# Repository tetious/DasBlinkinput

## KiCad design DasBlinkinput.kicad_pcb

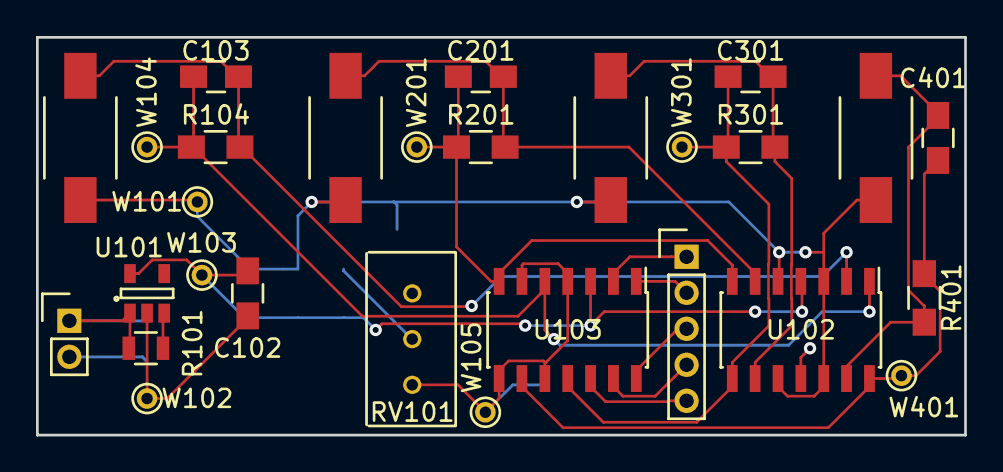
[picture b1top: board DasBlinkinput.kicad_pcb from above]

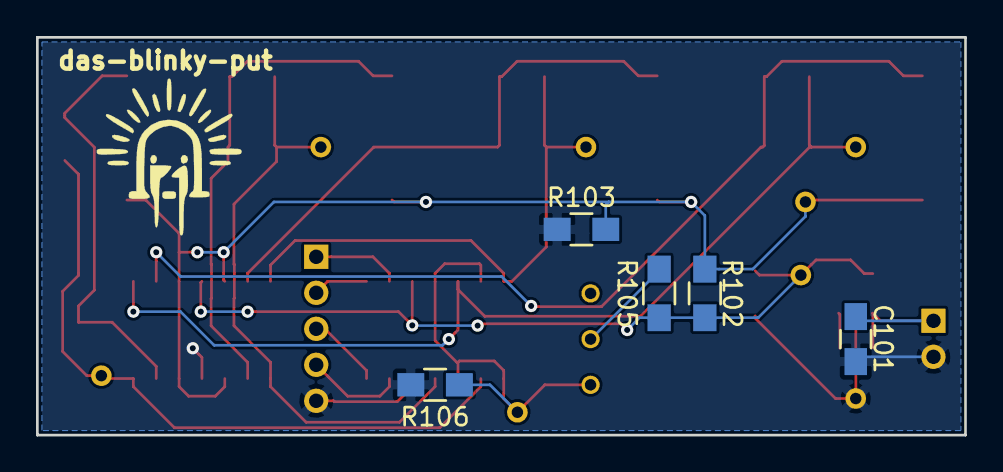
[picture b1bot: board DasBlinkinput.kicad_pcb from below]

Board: 2 copper layers, 51.6 x 22.1 mm, 33 parts (5 on the bottom side), 19 nets.

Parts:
C101: 1u; C_0805_HandSoldering
C102: .1u; C_0805_HandSoldering
C103, C201, C301, C401: 100p; C_0805_HandSoldering
P101: CONN_01X02; Pin_Header_Straight_1x02_Pitch2.00mm
P102: CONN_01X05; Pin_Header_Straight_1x05_Pitch2.00mm
PD101, PD201, PD301, PD401: QSB34CGR; PD_QSB34
R101: 0; R_0805
R102, R103, R105, R106: 10k; R_0805_HandSoldering
R104, R201, R301, R401: 1M; R_0805_HandSoldering
RV101: POT; 3296W_POT
U101: MIC5501; SOT-23-5
U102: MCP6404; SOIC-14_3.9x8.7mm_Pitch1.27mm
U103: LM339; SOIC-14_3.9x8.7mm_Pitch1.27mm
W101: VGND; PINTST
W102: GND; PINTST
W103: +3v; PINTST
W104, W201, W301, W401: C; PINTST
W105: REF; PINTST

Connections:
/+3v: C102.2, R102.1, R105.1, U101.5, U102.4, U103.3, W103.1
/Channel2/C_OUT: P102.2, U103.1
/Channel2/REF_IN: R106.1, RV101.3, U103.4, U103.6, U103.8, U103.10, W105.1
/Channel3/C_OUT: P102.3, U103.14
/Channel4/C_OUT: P102.4, U103.13
GND: C101.2, C102.1, P101.2, P102.5, R103.2, R106.2, U101.2, U102.11, U103.12, W102.1
unnamed: C101.1, P101.1, R101.1, U101.1
unnamed: C103.1, R104.1, U102.1, U103.5, W104.1
unnamed: C103.2, PD101.1, R104.2, U102.2
unnamed: C201.1, R201.1, U102.7, U103.7, W201.1
unnamed: C201.2, PD201.1, R201.2, U102.6
unnamed: C301.1, R301.1, U102.8, U103.11, W301.1
unnamed: C301.2, PD301.1, R301.2, U102.9
unnamed: C401.1, R401.1, U102.14, U103.9, W401.1
unnamed: C401.2, PD401.1, R401.2, U102.13
unnamed: P102.1, U103.2
unnamed: R101.2, U101.3
unnamed: R105.2, RV101.2
VGND: PD101.2, PD201.2, PD301.2, PD401.2, R102.2, R103.1, U102.3, U102.5, U102.10, U102.12, W101.1

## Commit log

2016-07-27 Initial checkin. Complete schematic.
2016-07-27 Name TPs
2016-07-27 Cleanups.
2016-07-27 Cleanups and footprint assignments.
2016-07-28 First iteration of layout.
2016-07-29 Final board, with BOM.
